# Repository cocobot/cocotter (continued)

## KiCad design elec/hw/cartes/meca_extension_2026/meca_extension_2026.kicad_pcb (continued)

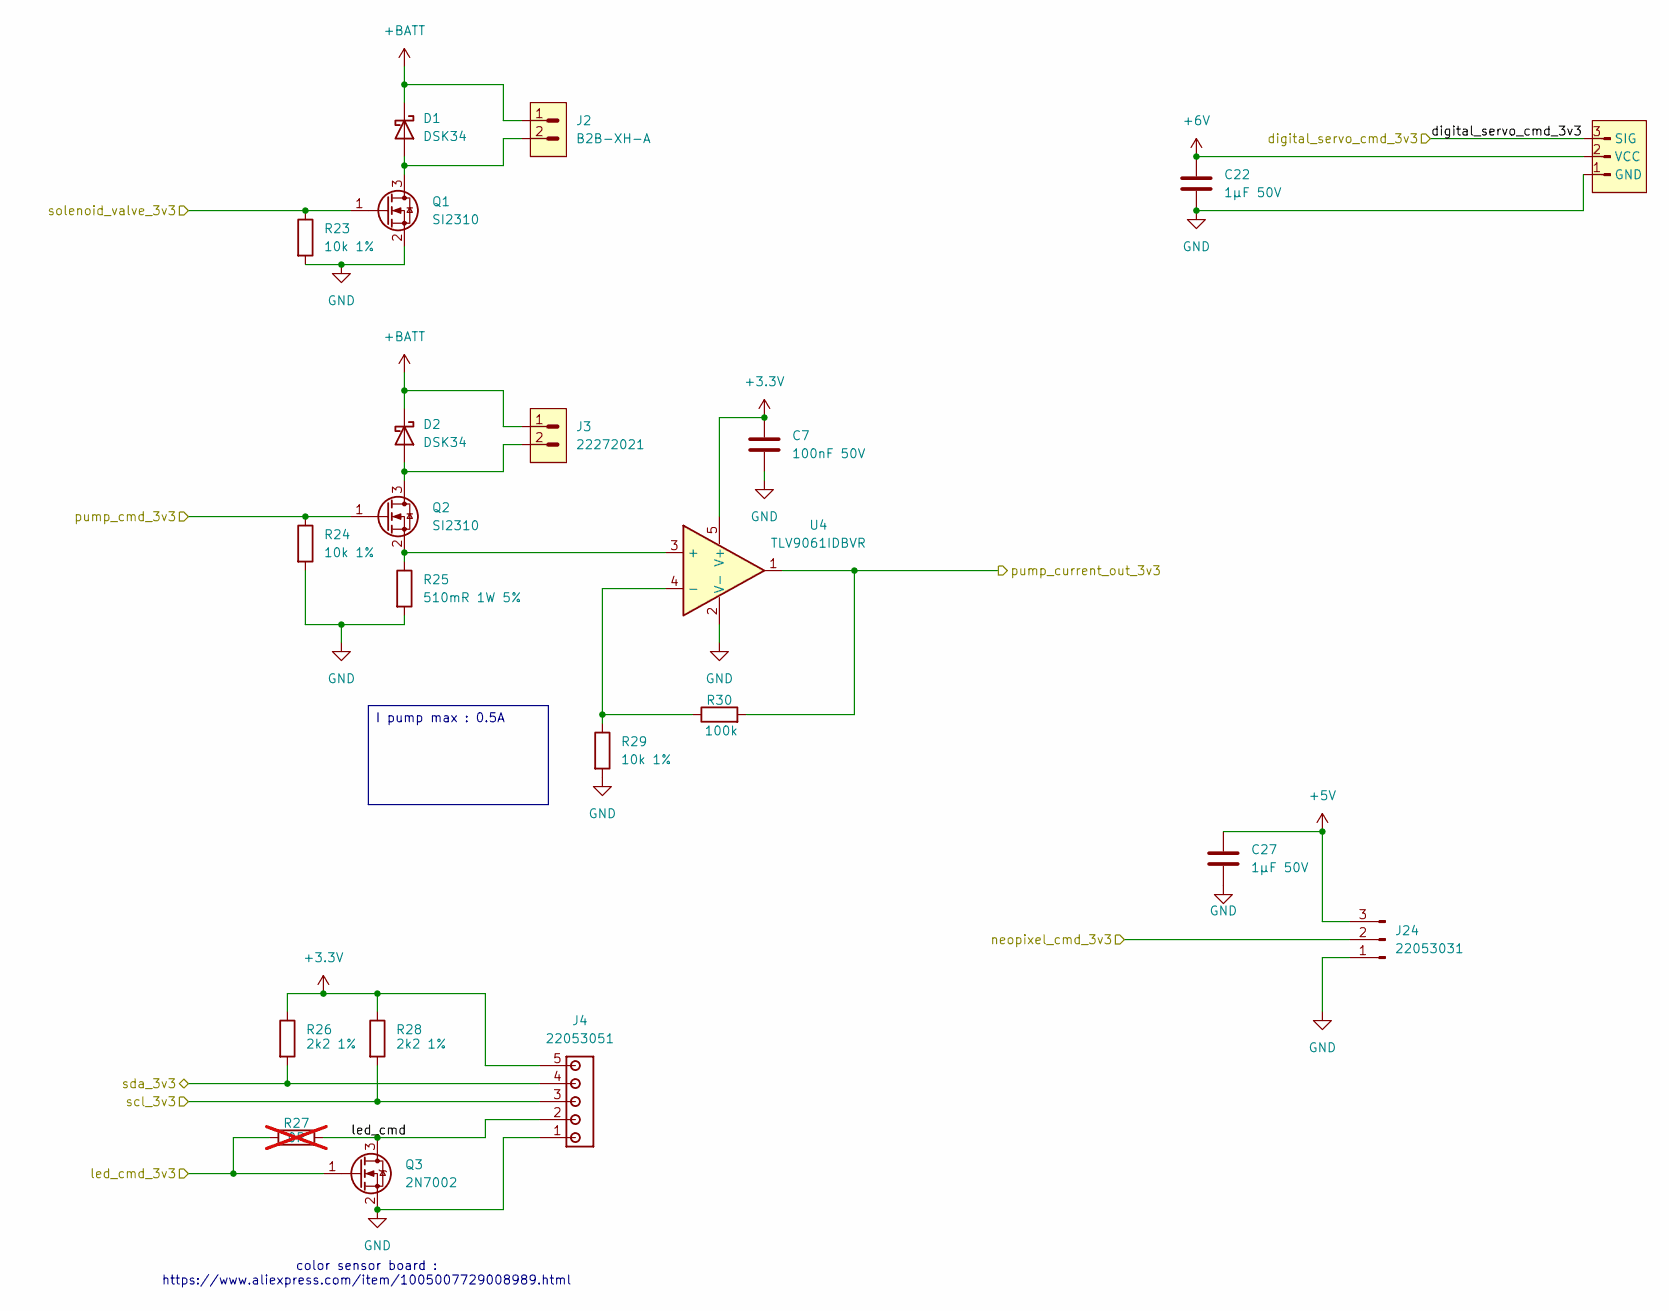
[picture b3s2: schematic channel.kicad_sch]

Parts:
C7: 100nF 50V; C_0603_1608Metric; JLCPCB Part # C14663
C22, C27: 1µF 50V; C_0805_2012Metric; JLCPCB Part # C28323
D1, D2: DSK34; D_SOD-123; JLCPCB Part # C727076
J2: B2B-XH-A; JLCPCB Part # C293316
J3: 22272021; JLCPCB Part # C293316
J4: 22053051; JLCPCB Part # C586992
J17: 5267-3P; JLC C49023819
J24: 22053031; JLCPCB Part # C505040
Q1, Q2: SI2310; SOT-23-3; JLCPCB Part # C2938374
Q3: 2N7002; SOT-23-3; JLCPCB Part # C8545
R23, R24, R29: 10k 1%; r0603_reflow; mouser 603-RC0603FR-10100KL
R25: 510mR 1W 5%; r2512_reflow; JLCPCB Part # C49656265
R26, R28: 2k2 1%; r0603_reflow; mouser 603-RC0603FR-10100KL
R27: 0R; r0603_reflow; JLCPCB Part # C431718; not fitted
R30: 100k; r0603_reflow; mouser 603-RC0603FR-10100KL
U4: TLV9061IDBVR; SOT-23-5; JLCPCB Part # C398358

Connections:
+3.3V: C7.1, J4.5, R26.1, R28.1, U4.5 (V+); also elsewhere on the board
+5V: C27.1, J24.3; also elsewhere on the board
+6V: C22.1, J17.2 (VCC); also elsewhere on the board
+BATT: D1.1 (K), D2.1 (K), J2.1, J3.1; also elsewhere on the board
/channel_0/led_cmd: J4.2, Q3.3 (D), R27.2
/color_led_cmd_3v3: Q3.1 (G), R27.1; also elsewhere on the board
/digital_servo_cmd_3v3: J17.3 (SIG); also elsewhere on the board
/neopixel_cmd_0_5v: J24.2; also elsewhere on the board
/pmp_cmd_0_3v3: Q2.1 (G), R24.1; also elsewhere on the board
/pump_current_0_3v3: R30.2, U4.1; also elsewhere on the board
/scl_0_3v3: J4.3, R28.2; also elsewhere on the board
/sda_0_3v3: J4.4, R26.2; also elsewhere on the board
/solenoid_valve_cmd_0_3v3: Q1.1 (G), R23.1; also elsewhere on the board
GND: C7.2, C22.2, C27.2, J4.1, J17.1 (GND), J24.1, Q1.2 (S), Q3.2 (S), R23.2, R24.2, R25.2, R29.2, U4.2 (V-); also elsewhere on the board
unnamed: D1.2 (A), J2.2, Q1.3 (D)
unnamed: D2.2 (A), J3.2, Q2.3 (D)
unnamed: Q2.2 (S), R25.1, U4.3 (+)
unnamed: R29.1, R30.1, U4.4 (-)

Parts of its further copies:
C8, C9, C10: 100nF 50V; C_0603_1608Metric; JLCPCB Part # C14663
C23, C24, C25, C29, C30, C31: 1µF 50V; C_0805_2012Metric; JLCPCB Part # C28323
D3, D4, D5, D6, D7, D8: DSK34; D_SOD-123; JLCPCB Part # C727076
J5, J8, J11: B2B-XH-A; JLCPCB Part # C293316
J6, J9, J12: 22272021; JLCPCB Part # C293316
J7, J10, J13: 22053051; JLCPCB Part # C586992
J18, J19, J20: 5267-3P; JLC C49023819
J25, J28, J29: 22053031; JLCPCB Part # C505040
Q4, Q5, Q7, Q8, Q10, Q11: SI2310; SOT-23-3; JLCPCB Part # C2938374
Q6, Q9, Q12: 2N7002; SOT-23-3; JLCPCB Part # C8545
R31, R32, R37, R39, R40, R45, R47, R48, R53: 10k 1%; r0603_reflow; mouser 603-RC0603FR-10100KL
R33, R41, R49: 510mR 1W 5%; r2512_reflow; JLCPCB Part # C49656265
R34, R36, R42, R44, R50, R52: 2k2 1%; r0603_reflow; mouser 603-RC0603FR-10100KL
R35, R43, R51: 0R; r0603_reflow; JLCPCB Part # C431718; not fitted
R38, R46, R54: 100k; r0603_reflow; mouser 603-RC0603FR-10100KL
U5, U6, U7: TLV9061IDBVR; SOT-23-5; JLCPCB Part # C398358

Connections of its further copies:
+3.3V: C8.1, C9.1, C10.1, J7.5, J10.5, J13.5, R34.1, R36.1, R42.1, R44.1, R50.1, R52.1, U5.5 (V+), U6.5 (V+), U7.5 (V+); also elsewhere on the board
+5V: C29.1, C30.1, C31.1, J25.3, J28.3, J29.3; also elsewhere on the board
+6V: C23.1, C24.1, C25.1, J18.2 (VCC), J19.2 (VCC), J20.2 (VCC); also elsewhere on the board
+BATT: D3.1 (K), D4.1 (K), D5.1 (K), D6.1 (K), D7.1 (K), D8.1 (K), J5.1, J6.1, J8.1, J9.1, J11.1, J12.1; also elsewhere on the board
/channel_1/led_cmd: J7.2, Q6.3 (D), R35.2
/channel_2/led_cmd: J10.2, Q9.3 (D), R43.2
/channel_3/led_cmd: J13.2, Q12.3 (D), R51.2
/color_led_cmd_3v3: Q6.1 (G), Q9.1 (G), Q12.1 (G), R35.1, R43.1, R51.1; also elsewhere on the board
/digital_servo_cmd_3v3: J18.3 (SIG), J19.3 (SIG), J20.3 (SIG); also elsewhere on the board
/neopixel_cmd_1_5v: J25.2; also elsewhere on the board
/neopixel_cmd_2_5v: J28.2; also elsewhere on the board
/neopixel_cmd_3_5v: J29.2; also elsewhere on the board
/pmp_cmd_1_3v3: Q5.1 (G), R32.1; also elsewhere on the board
/pmp_cmd_2_3v3: Q8.1 (G), R40.1; also elsewhere on the board
/pmp_cmd_3_3v3: Q11.1 (G), R48.1; also elsewhere on the board
/pump_current_1_3v3: R38.2, U5.1; also elsewhere on the board
/pump_current_2_3v3: R46.2, U6.1; also elsewhere on the board
/pump_current_3_3v3: R54.2, U7.1; also elsewhere on the board
/scl_1_3v3: J7.3, R36.2; also elsewhere on the board
/scl_2_3v3: J10.3, R44.2; also elsewhere on the board
/scl_3_3v3: J13.3, R52.2; also elsewhere on the board
/sda_1_3v3: J7.4, R34.2; also elsewhere on the board
/sda_2_3v3: J10.4, R42.2; also elsewhere on the board
/sda_3_3v3: J13.4, R50.2; also elsewhere on the board
/solenoid_valve_cmd_1_3v3: Q4.1 (G), R31.1; also elsewhere on the board
/solenoid_valve_cmd_2_3v3: Q7.1 (G), R39.1; also elsewhere on the board
/solenoid_valve_cmd_3_3v3: Q10.1 (G), R47.1; also elsewhere on the board
GND: C8.2, C9.2, C10.2, C23.2, C24.2, C25.2, C29.2, C30.2, C31.2, J7.1, J10.1, J13.1, J18.1 (GND), J19.1 (GND), J20.1 (GND), J25.1, J28.1, J29.1, Q4.2 (S), Q6.2 (S), Q7.2 (S), Q9.2 (S), Q10.2 (S), Q12.2 (S), R31.2, R32.2, R33.2, R37.2, R39.2, R40.2, R41.2, R45.2, R47.2, R48.2, R49.2, R53.2, U5.2 (V-), U6.2 (V-), U7.2 (V-); also elsewhere on the board
unnamed: D3.2 (A), J5.2, Q4.3 (D)
unnamed: D4.2 (A), J6.2, Q5.3 (D)
unnamed: D5.2 (A), J8.2, Q7.3 (D)
unnamed: D6.2 (A), J9.2, Q8.3 (D)
unnamed: D7.2 (A), J11.2, Q10.3 (D)
unnamed: D8.2 (A), J12.2, Q11.3 (D)
unnamed: Q5.2 (S), R33.1, U5.3 (+)
unnamed: Q8.2 (S), R41.1, U6.3 (+)
unnamed: Q11.2 (S), R49.1, U7.3 (+)
unnamed: R37.1, R38.1, U5.4 (-)
unnamed: R45.1, R46.1, U6.4 (-)
unnamed: R53.1, R54.1, U7.4 (-)

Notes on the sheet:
color sensor board : https://www.aliexpress.com/item/1005007729008989.html
I pump max : 0.5A

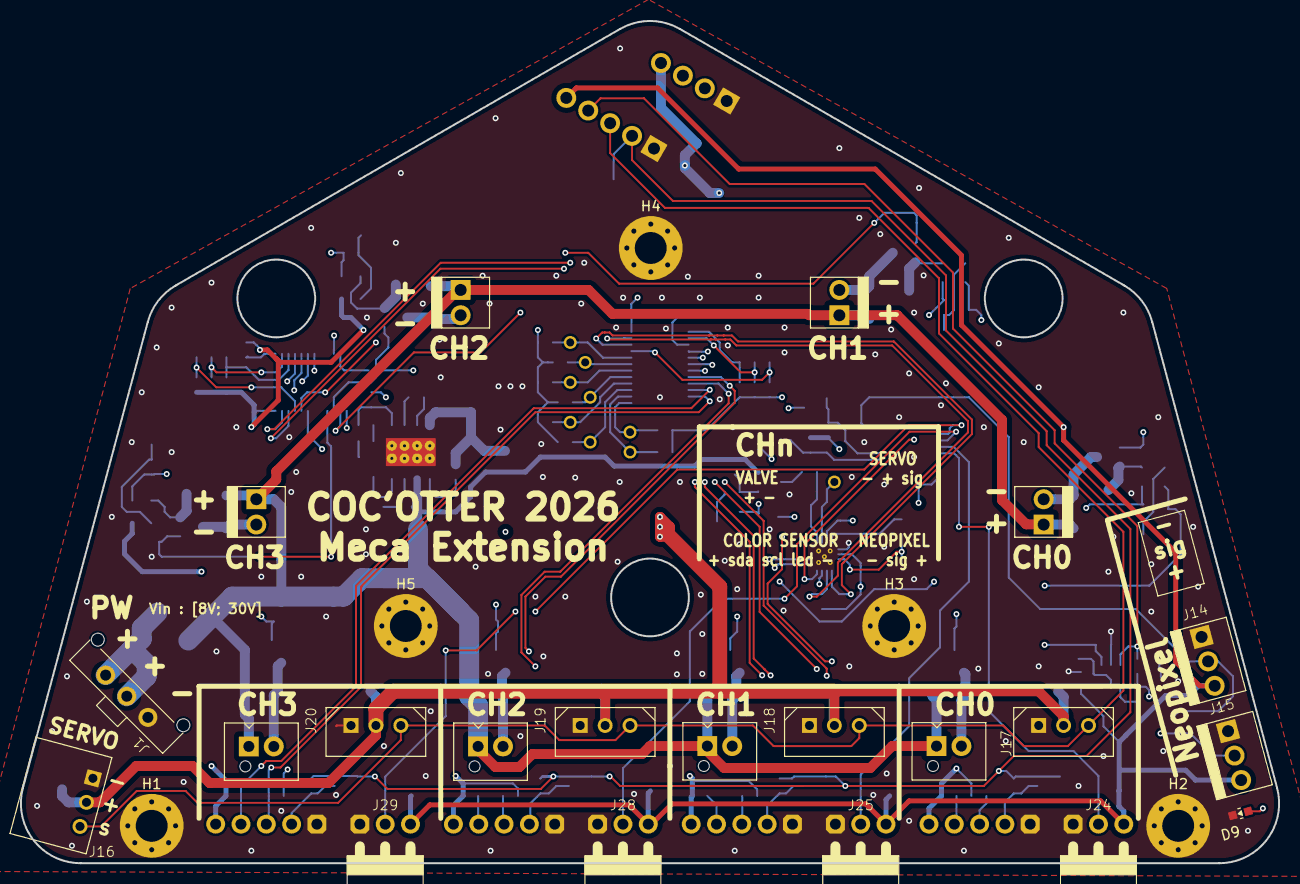
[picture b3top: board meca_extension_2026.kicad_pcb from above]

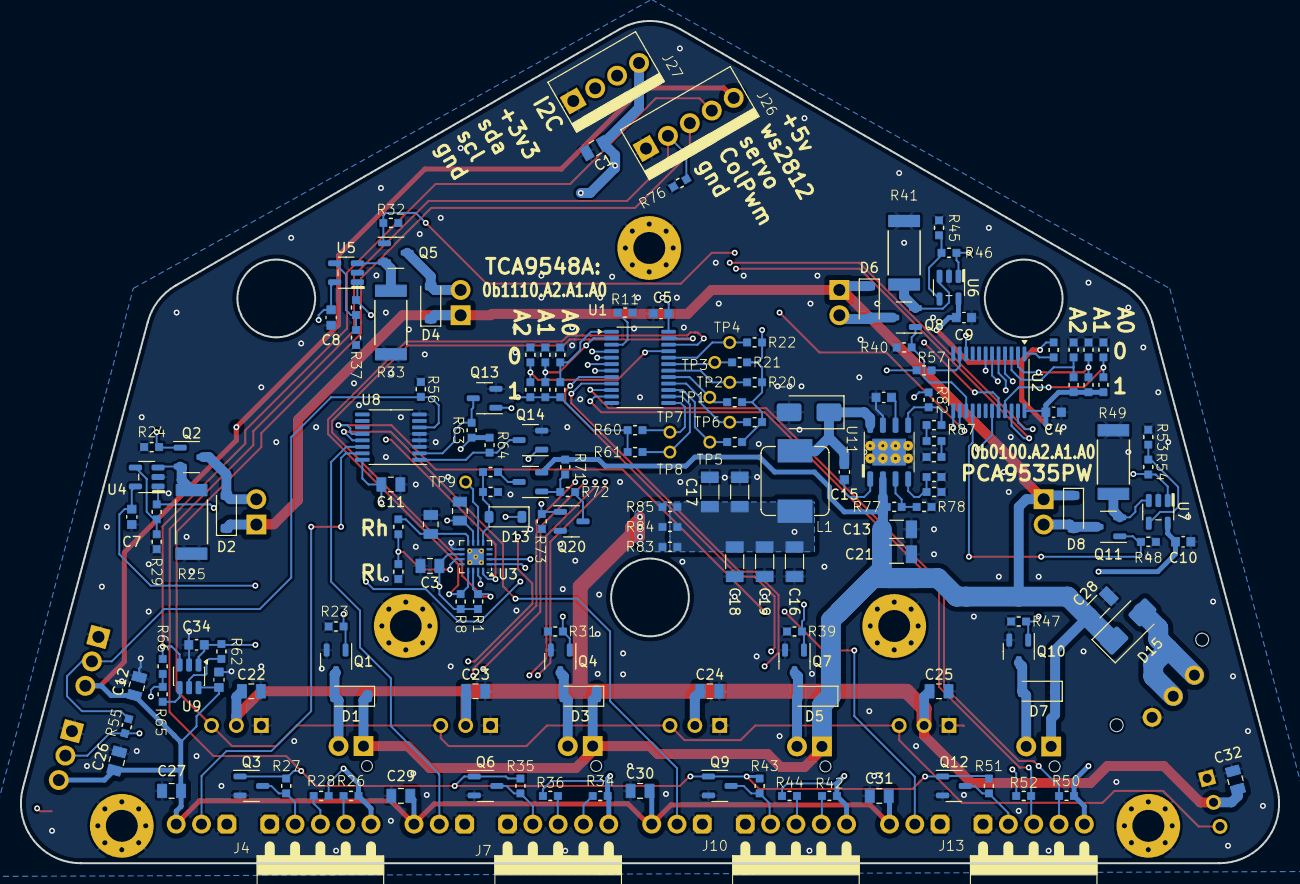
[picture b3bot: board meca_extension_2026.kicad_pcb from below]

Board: 4 copper layers, 126.2 x 84.5 mm, 196 parts (170 on the bottom side), 98 nets.

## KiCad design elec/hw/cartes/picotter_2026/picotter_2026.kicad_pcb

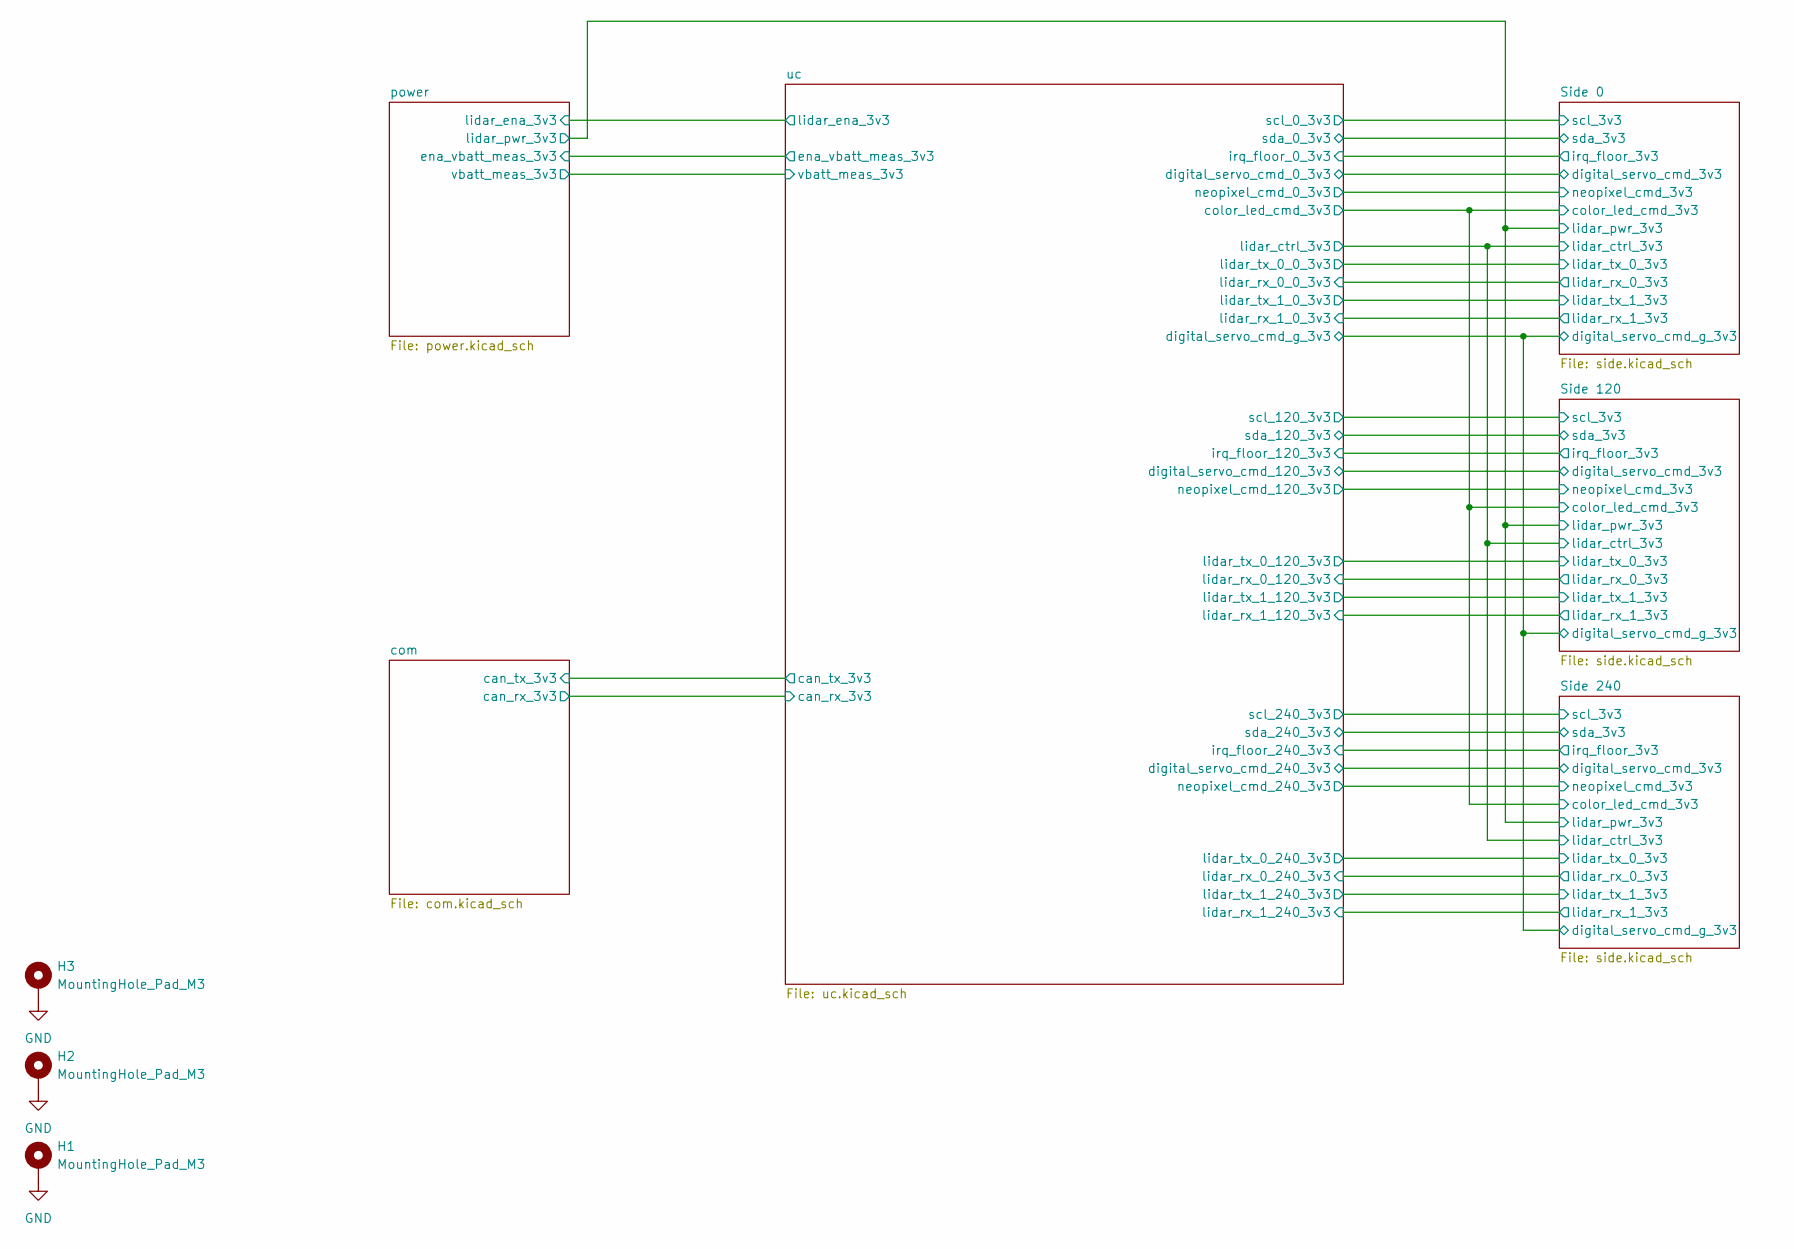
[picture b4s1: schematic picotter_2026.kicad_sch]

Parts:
H1, H2, H3: MountingHole_Pad_M3; MountingHole_3.2mm_M3_Pad_Via

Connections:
GND: H1.1, H2.1, H3.1; also elsewhere on the board

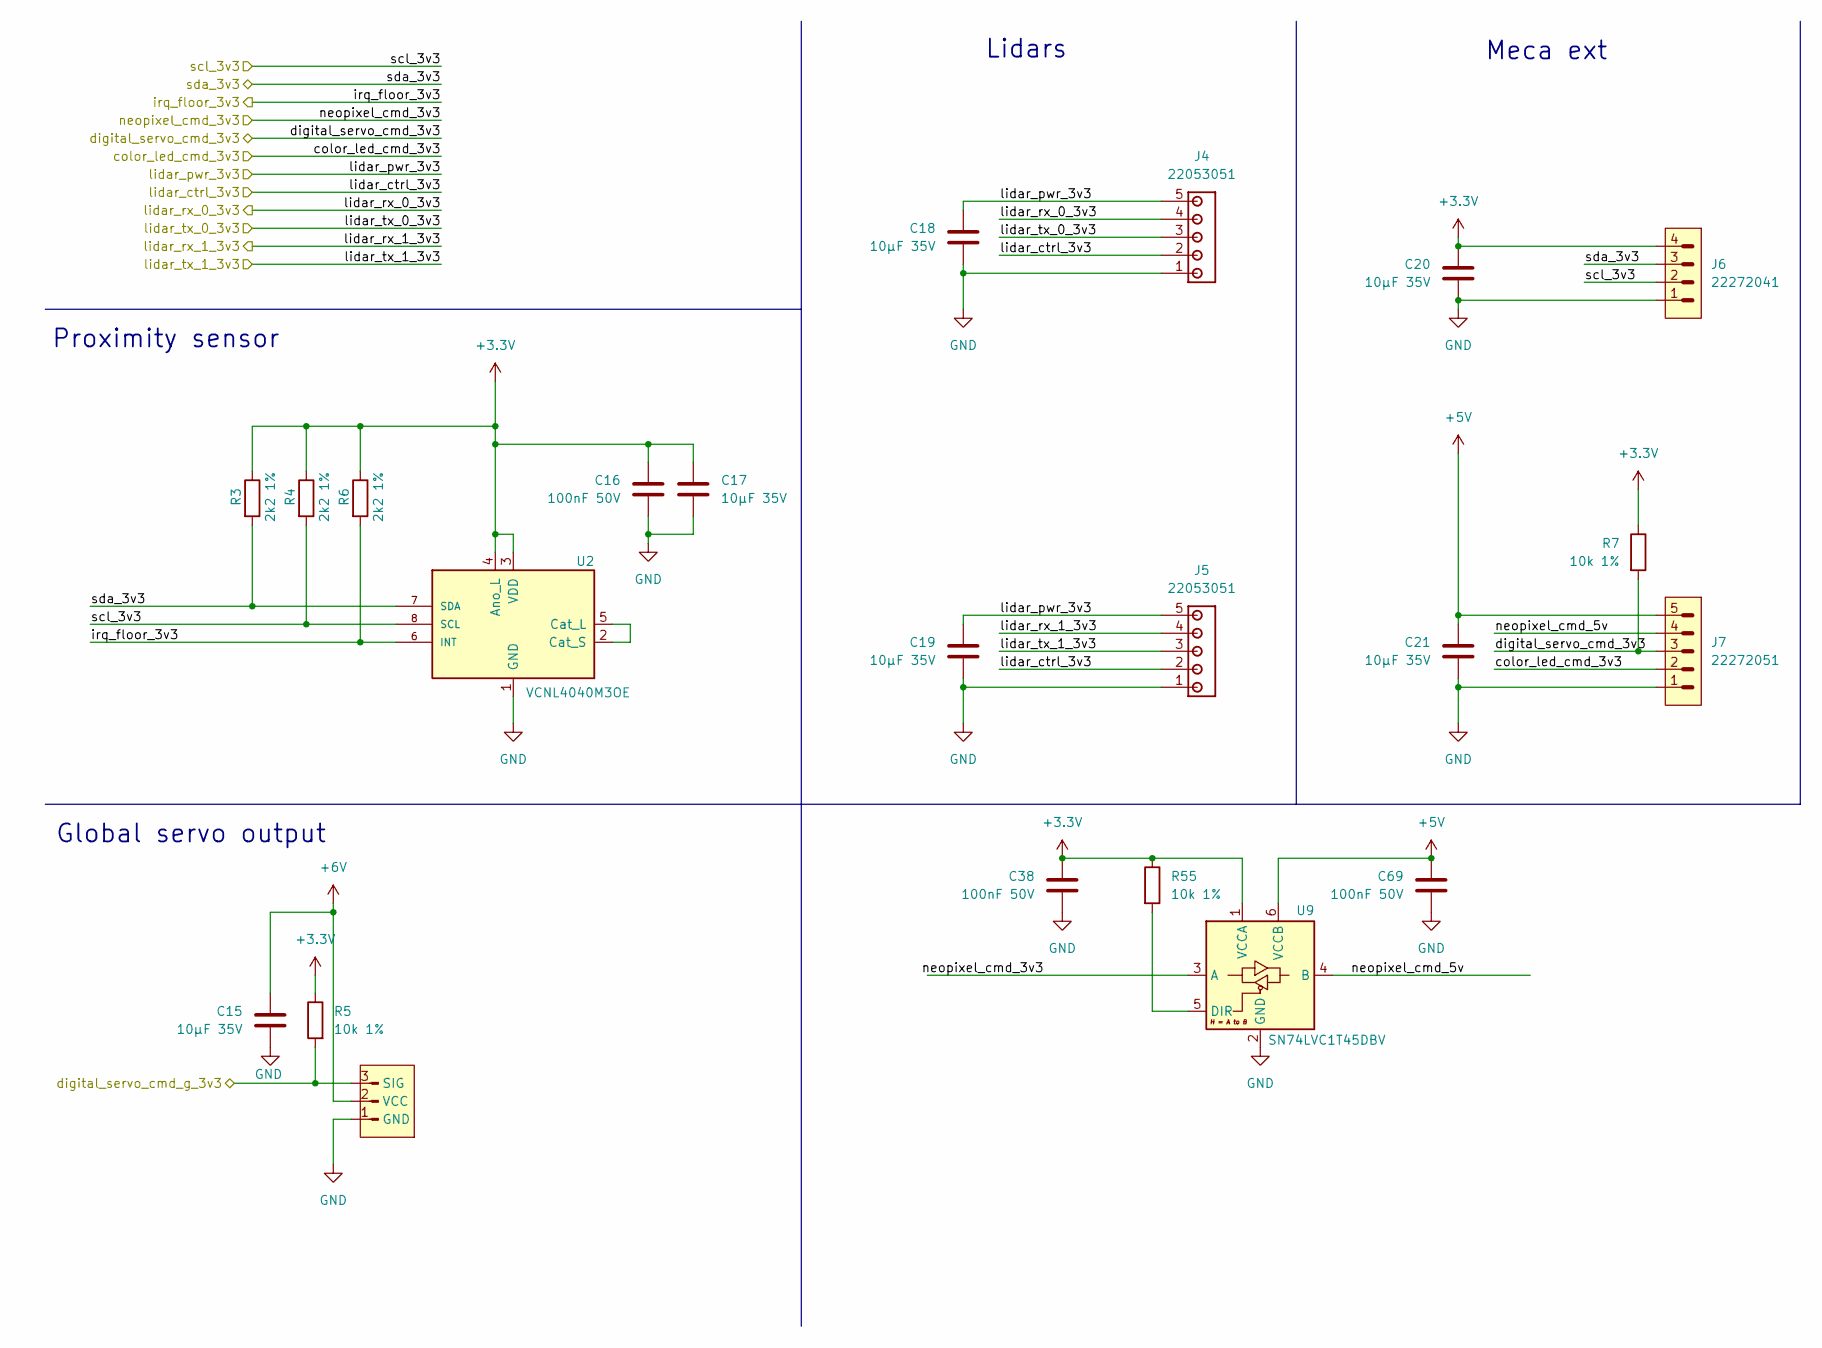
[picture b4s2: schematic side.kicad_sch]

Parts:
C15, C17, C18, C19, C20, C21: 10µF 35V; C_1206_3216Metric; jlcpcb C454102
C16, C38, C69: 100nF 50V; C_0603_1608Metric; JLCPCB Part # C14663
J3: 5264-3P; JLC C49023819
J4, J5: 22053051; JLCPCB Part # C586992
J6: 22272041; JLCPCB Part # C504991
J7: 22272051; JLCPCB Part # C585785
R3, R4, R6: 2k2 1%; r0603_reflow; mouser 603-RC0603FR-10100KL
R5, R7, R55: 10k 1%; r0603_reflow; mouser 603-RC0603FR-10100KL
U2: VCNL4040M3OE; VISHAY_VCNL4040_4X2X1.1; DigiKey_Part_Number VCNL4040M3OECT-ND
U9: SN74LVC1T45DBV; SOT-23-6; JLCPCB Part # C7843

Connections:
+3.3V: C16.1, C17.1, C20.1, C38.1, J6.4, R3.1, R4.1, R5.1, R6.1, R7.1, R55.1, U2.3 (VDD), U2.4 (Ano_L), U9.1 (VCCA); also elsewhere on the board
+5V: C21.1, C69.1, J7.5, U9.6 (VCCB); also elsewhere on the board
+6V: C15.1, J3.2 (VCC); also elsewhere on the board
/Side 0/color_led_cmd_3v3: J7.2; also elsewhere on the board
/Side 0/digital_servo_cmd_3v3: J7.3, R7.2; also elsewhere on the board
/Side 0/digital_servo_cmd_g_3v3: J3.3 (SIG), R5.2; also elsewhere on the board
/Side 0/irq_floor_3v3: R6.2, U2.6 (INT); also elsewhere on the board
/Side 0/lidar_ctrl_3v3: J4.2, J5.2; also elsewhere on the board
/Side 0/lidar_pwr_3v3: C18.1, C19.1, J4.5, J5.5; also elsewhere on the board
/Side 0/lidar_rx_0_3v3: J4.4; also elsewhere on the board
/Side 0/lidar_rx_1_3v3: J5.4; also elsewhere on the board
/Side 0/lidar_tx_0_3v3: J4.3; also elsewhere on the board
/Side 0/lidar_tx_1_3v3: J5.3; also elsewhere on the board
/Side 0/neopixel_cmd_3v3: U9.3 (A); also elsewhere on the board
/Side 0/neopixel_cmd_5v: J7.4, U9.4 (B)
/Side 0/scl_3v3: J6.2, R4.2, U2.8 (SCL); also elsewhere on the board
/Side 0/sda_3v3: J6.3, R3.2, U2.7 (SDA); also elsewhere on the board
GND: C15.2, C16.2, C17.2, C18.2, C19.2, C20.2, C21.2, C38.2, C69.2, J3.1 (GND), J4.1, J5.1, J6.1, J7.1, U2.1 (GND), U9.2 (GND); also elsewhere on the board
unnamed: U2.2 (Cat_S), U2.5 (Cat_L)
unnamed: R55.2, U9.5 (DIR)

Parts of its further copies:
C22, C24, C25, C26, C27, C28, C29, C31, C32, C33, C34, C35: 10µF 35V; C_1206_3216Metric; jlcpcb C454102
C23, C30, C67, C68, C70, C71: 100nF 50V; C_0603_1608Metric; JLCPCB Part # C14663
J8, J13: 5264-3P; JLC C49023819
J9, J10, J14, J15: 22053051; JLCPCB Part # C586992
J11, J16: 22272041; JLCPCB Part # C504991
J12, J17: 22272051; JLCPCB Part # C585785
R8, R9, R11, R13, R14, R16: 2k2 1%; r0603_reflow; mouser 603-RC0603FR-10100KL
R10, R12, R15, R17, R56, R57: 10k 1%; r0603_reflow; mouser 603-RC0603FR-10100KL
U3, U4: VCNL4040M3OE; VISHAY_VCNL4040_4X2X1.1; DigiKey_Part_Number VCNL4040M3OECT-ND
U10, U11: SN74LVC1T45DBV; SOT-23-6; JLCPCB Part # C7843

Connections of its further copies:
+3.3V: C23.1, C24.1, C27.1, C30.1, C31.1, C34.1, C67.1, C68.1, J11.4, J16.4, R8.1, R9.1, R10.1, R11.1, R12.1, R13.1, R14.1, R15.1, R16.1, R17.1, R56.1, R57.1, U3.3 (VDD), U3.4 (Ano_L), U4.3 (VDD), U4.4 (Ano_L), U10.1 (VCCA), U11.1 (VCCA); also elsewhere on the board
+5V: C28.1, C35.1, C70.1, C71.1, J12.5, J17.5, U10.6 (VCCB), U11.6 (VCCB); also elsewhere on the board
+6V: C22.1, C29.1, J8.2 (VCC), J13.2 (VCC); also elsewhere on the board
/Side 0/color_led_cmd_3v3: J12.2, J17.2; also elsewhere on the board
/Side 0/digital_servo_cmd_g_3v3: J8.3 (SIG), J13.3 (SIG), R10.2, R15.2; also elsewhere on the board
/Side 0/lidar_ctrl_3v3: J9.2, J10.2, J14.2, J15.2; also elsewhere on the board
/Side 0/lidar_pwr_3v3: C25.1, C26.1, C32.1, C33.1, J9.5, J10.5, J14.5, J15.5; also elsewhere on the board
/Side 120/digital_servo_cmd_3v3: J12.3, R12.2; also elsewhere on the board
/Side 120/irq_floor_3v3: R11.2, U3.6 (INT); also elsewhere on the board
/Side 120/lidar_rx_0_3v3: J9.4; also elsewhere on the board
/Side 120/lidar_rx_1_3v3: J10.4; also elsewhere on the board
/Side 120/lidar_tx_0_3v3: J9.3; also elsewhere on the board
/Side 120/lidar_tx_1_3v3: J10.3; also elsewhere on the board
/Side 120/neopixel_cmd_3v3: U10.3 (A); also elsewhere on the board
/Side 120/neopixel_cmd_5v: J12.4, U10.4 (B)
/Side 120/scl_3v3: J11.2, R9.2, U3.8 (SCL); also elsewhere on the board
/Side 120/sda_3v3: J11.3, R8.2, U3.7 (SDA); also elsewhere on the board
/Side 240/digital_servo_cmd_3v3: J17.3, R17.2; also elsewhere on the board
/Side 240/irq_floor_3v3: R16.2, U4.6 (INT); also elsewhere on the board
/Side 240/lidar_rx_0_3v3: J14.4; also elsewhere on the board
/Side 240/lidar_rx_1_3v3: J15.4; also elsewhere on the board
/Side 240/lidar_tx_0_3v3: J14.3; also elsewhere on the board
/Side 240/lidar_tx_1_3v3: J15.3; also elsewhere on the board
/Side 240/neopixel_cmd_3v3: U11.3 (A); also elsewhere on the board
/Side 240/neopixel_cmd_5v: J17.4, U11.4 (B)
/Side 240/scl_3v3: J16.2, R14.2, U4.8 (SCL); also elsewhere on the board
/Side 240/sda_3v3: J16.3, R13.2, U4.7 (SDA); also elsewhere on the board
GND: C22.2, C23.2, C24.2, C25.2, C26.2, C27.2, C28.2, C29.2, C30.2, C31.2, C32.2, C33.2, C34.2, C35.2, C67.2, C68.2, C70.2, C71.2, J8.1 (GND), J9.1, J10.1, J11.1, J12.1, J13.1 (GND), J14.1, J15.1, J16.1, J17.1, U3.1 (GND), U4.1 (GND), U10.2 (GND), U11.2 (GND); also elsewhere on the board
unnamed: U3.2 (Cat_S), U3.5 (Cat_L)
unnamed: U4.2 (Cat_S), U4.5 (Cat_L)
unnamed: R56.2, U10.5 (DIR)
unnamed: R57.2, U11.5 (DIR)

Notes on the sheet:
Meca ext
Lidars
Global servo output
Proximity sensor

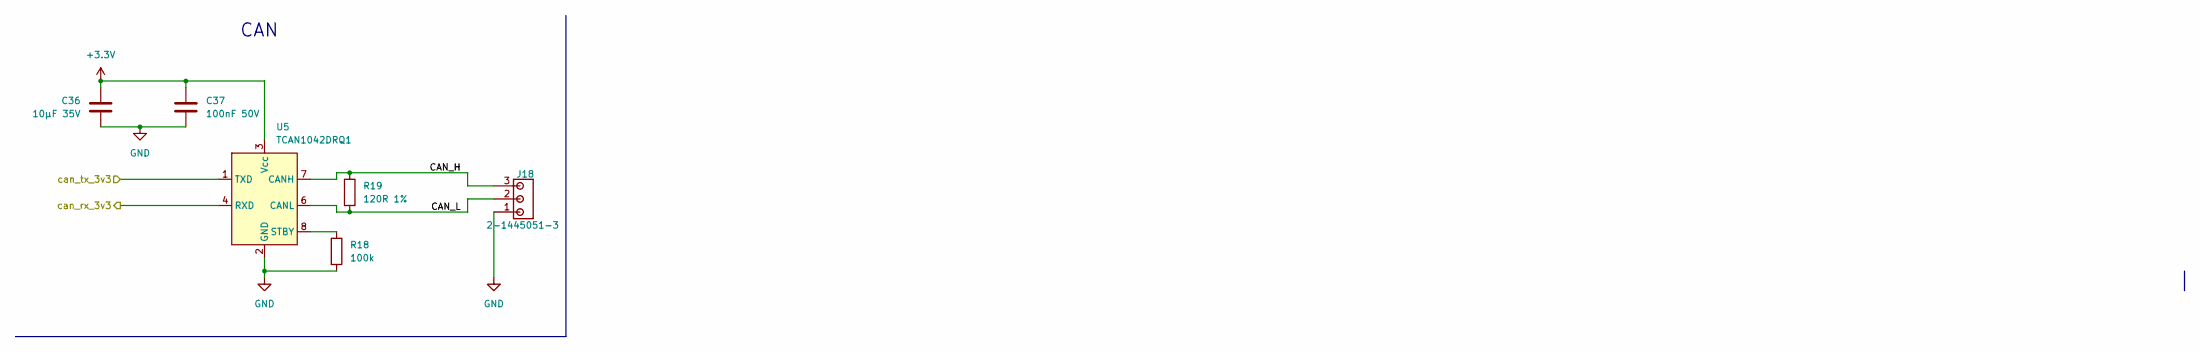
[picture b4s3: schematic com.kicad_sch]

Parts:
C36: 10µF 35V; C_1206_3216Metric; jlcpcb C454102
C37: 100nF 50V; C_0603_1608Metric; JLCPCB Part # C14663
J18: 2-1445051-3; JLCPCB Part # C17473329
R18: 100k; r0603_reflow; mouser 603-RC0603FR-10100KL
R19: 120R 1%; r1206_reflow; JLCPCB Part # C17909
U5: TCAN1042DRQ1; D0008A; JLCPCB Part # C118837

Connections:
+3.3V: C36.1, C37.1, U5.3 (Vcc); also elsewhere on the board
/com/CAN_H: J18.3, R19.1, U5.7 (CANH)
/com/CAN_L: J18.2, R19.2, U5.6 (CANL)
/com/can_rx_3v3: U5.4 (RXD); also elsewhere on the board
/com/can_tx_3v3: U5.1 (TXD); also elsewhere on the board
GND: C36.2, C37.2, J18.1, R18.2, U5.2 (GND); also elsewhere on the board
unnamed: R18.1, U5.8 (STBY)

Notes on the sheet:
CAN

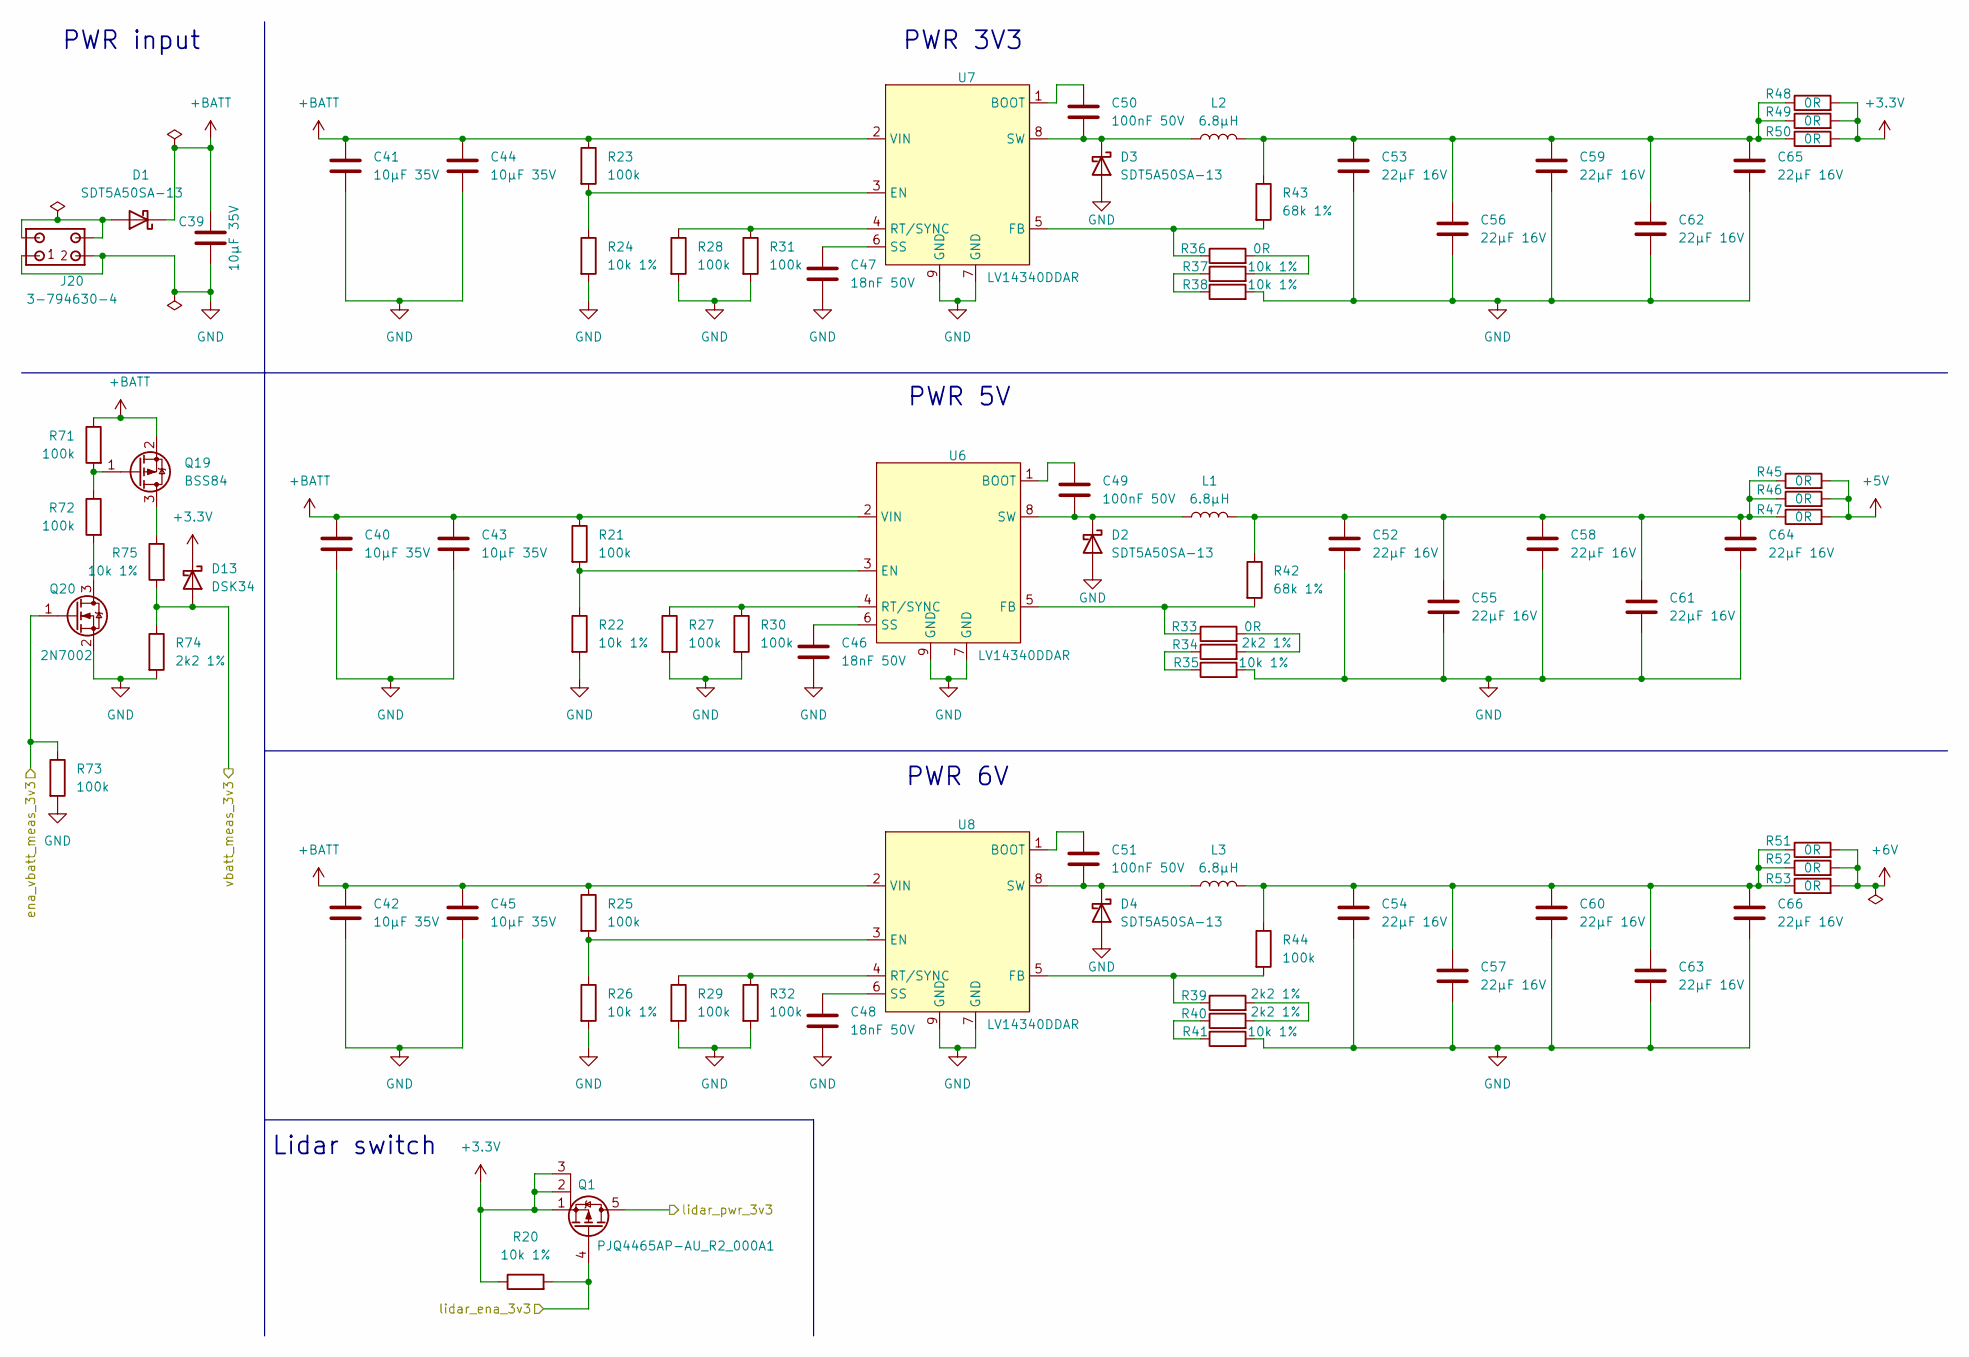
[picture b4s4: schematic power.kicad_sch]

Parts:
C39, C40, C41, C42, C43, C44, C45: 10µF 35V; C_1206_3216Metric; jlcpcb C454102
C46, C47, C48: 18nF 50V; C_0603_1608Metric; JLCPCB Part # C107079
C49, C50, C51: 100nF 50V; C_0603_1608Metric; JLCPCB Part # C14663
C52, C53, C54, C55, C56, C57, C58, C59, C60, C61, C62, C63, C64, C65, C66: 22µF 16V; C_1206_3216Metric
D1, D2, D3, D4: SDT5A50SA-13; D_SMA; JLCPCB Part # C6802582
D13: DSK34; D_SOD-123; JLCPCB Part # C727076
J20: 3-794630-4; JLCPCB Part # C5164688
L1, L2, L3: 6.8µH; BMRx00060630; JLCPCB Part # C2838323
Q1: PJQ4465AP-AU_R2_000A1; Diodes_PowerDI3333-8; JLCPCB Part # C6147631
Q19: BSS84; SOT-23-3
Q20: 2N7002; SOT-23-3; JLCPCB Part # C8545
R20, R22, R24, R26, R35, R37, R38, R41, R75: 10k 1%; r0603_reflow; mouser 603-RC0603FR-10100KL
R21, R23, R25, R27, R28, R29, R30, R31, R32, R44, R71, R72, R73: 100k; r0603_reflow; mouser 603-RC0603FR-10100KL
R33, R36, R45, R46, R47, R48, R49, R50, R51, R52, R53: 0R; r0603_reflow; JLCPCB Part # C431718
R34, R39, R40, R74: 2k2 1%; r0603_reflow; mouser 603-RC0603FR-10100KL
R42, R43: 68k 1%; r0603_reflow; JLCPCB Part # C23231
U6, U7, U8: LV14340DDAR; DDA0008B

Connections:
+3.3V: D13.1 (K), Q1.1 (S), Q1.2 (S), Q1.3 (S), R20.1, R48.2, R49.2, R50.2; also elsewhere on the board
+5V: R45.2, R46.2, R47.2; also elsewhere on the board
+6V: R51.2, R52.2, R53.2; also elsewhere on the board
+BATT: C39.1, C40.1, C41.1, C42.1, C43.1, C44.1, C45.1, D1.1 (K), Q19.2 (S), R21.1, R23.1, R25.1, R71.1, U6.2 (VIN), U7.2 (VIN), U8.2 (VIN)
/Side 0/lidar_pwr_3v3: Q1.5 (D); also elsewhere on the board
/power/ena_vbatt_meas_3v3: Q20.1 (G), R73.1; also elsewhere on the board
/power/lidar_ena_3v3: Q1.4 (G), R20.2; also elsewhere on the board
/power/vbatt_meas_3v3: D13.2 (A), R74.1, R75.2; also elsewhere on the board
GND: C39.2, C40.2, C41.2, C42.2, C43.2, C44.2, C45.2, C46.2, C47.2, C48.2, C52.2, C53.2, C54.2, C55.2, C56.2, C57.2, C58.2, C59.2, C60.2, C61.2, C62.2, C63.2, C64.2, C65.2, C66.2, D2.2 (A), D3.2 (A), D4.2 (A), J20.1, J20.2, Q20.2 (S), R22.2, R24.2, R26.2, R27.2, R28.2, R29.2, R30.2, R31.2, R32.2, R35.2, R38.2, R41.2, R73.2, R74.2, U6.7 (GND), U6.9 (GND), U7.7 (GND), U7.9 (GND), U8.7 (GND), U8.9 (GND); also elsewhere on the board
unnamed: C52.1, C55.1, C58.1, C61.1, C64.1, L1.2, R42.1, R45.1, R46.1, R47.1
unnamed: C53.1, C56.1, C59.1, C62.1, C65.1, L2.2, R43.1, R48.1, R49.1, R50.1
unnamed: C54.1, C57.1, C60.1, C63.1, C66.1, L3.2, R44.1, R51.1, R52.1, R53.1
unnamed: D1.2 (A), J20.3, J20.4
unnamed: C49.2, D2.1 (K), L1.1, U6.8 (SW)
unnamed: C50.2, D3.1 (K), L2.1, U7.8 (SW)
unnamed: C51.2, D4.1 (K), L3.1, U8.8 (SW)
unnamed: Q19.3 (D), R75.1
unnamed: Q19.1 (G), R71.2, R72.1
unnamed: Q20.3 (D), R72.2
unnamed: R33.2, R34.2
unnamed: R34.1, R35.1
unnamed: R36.2, R37.2
unnamed: R37.1, R38.1
unnamed: R39.2, R40.2
unnamed: R40.1, R41.1
unnamed: C49.1, U6.1 (BOOT)
unnamed: R21.2, R22.1, U6.3 (EN)
unnamed: R33.1, R42.2, U6.5 (FB)
unnamed: R27.1, R30.1, U6.4 (RT/SYNC)
unnamed: C46.1, U6.6 (SS)
unnamed: C50.1, U7.1 (BOOT)
unnamed: R23.2, R24.1, U7.3 (EN)
unnamed: R36.1, R43.2, U7.5 (FB)
unnamed: R28.1, R31.1, U7.4 (RT/SYNC)
unnamed: C47.1, U7.6 (SS)
unnamed: C51.1, U8.1 (BOOT)
unnamed: R25.2, R26.1, U8.3 (EN)
unnamed: R39.1, R44.2, U8.5 (FB)
unnamed: R29.1, R32.1, U8.4 (RT/SYNC)
unnamed: C48.1, U8.6 (SS)

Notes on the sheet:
Lidar switch
PWR input
PWR 5V
PWR 6V
PWR 3V3
